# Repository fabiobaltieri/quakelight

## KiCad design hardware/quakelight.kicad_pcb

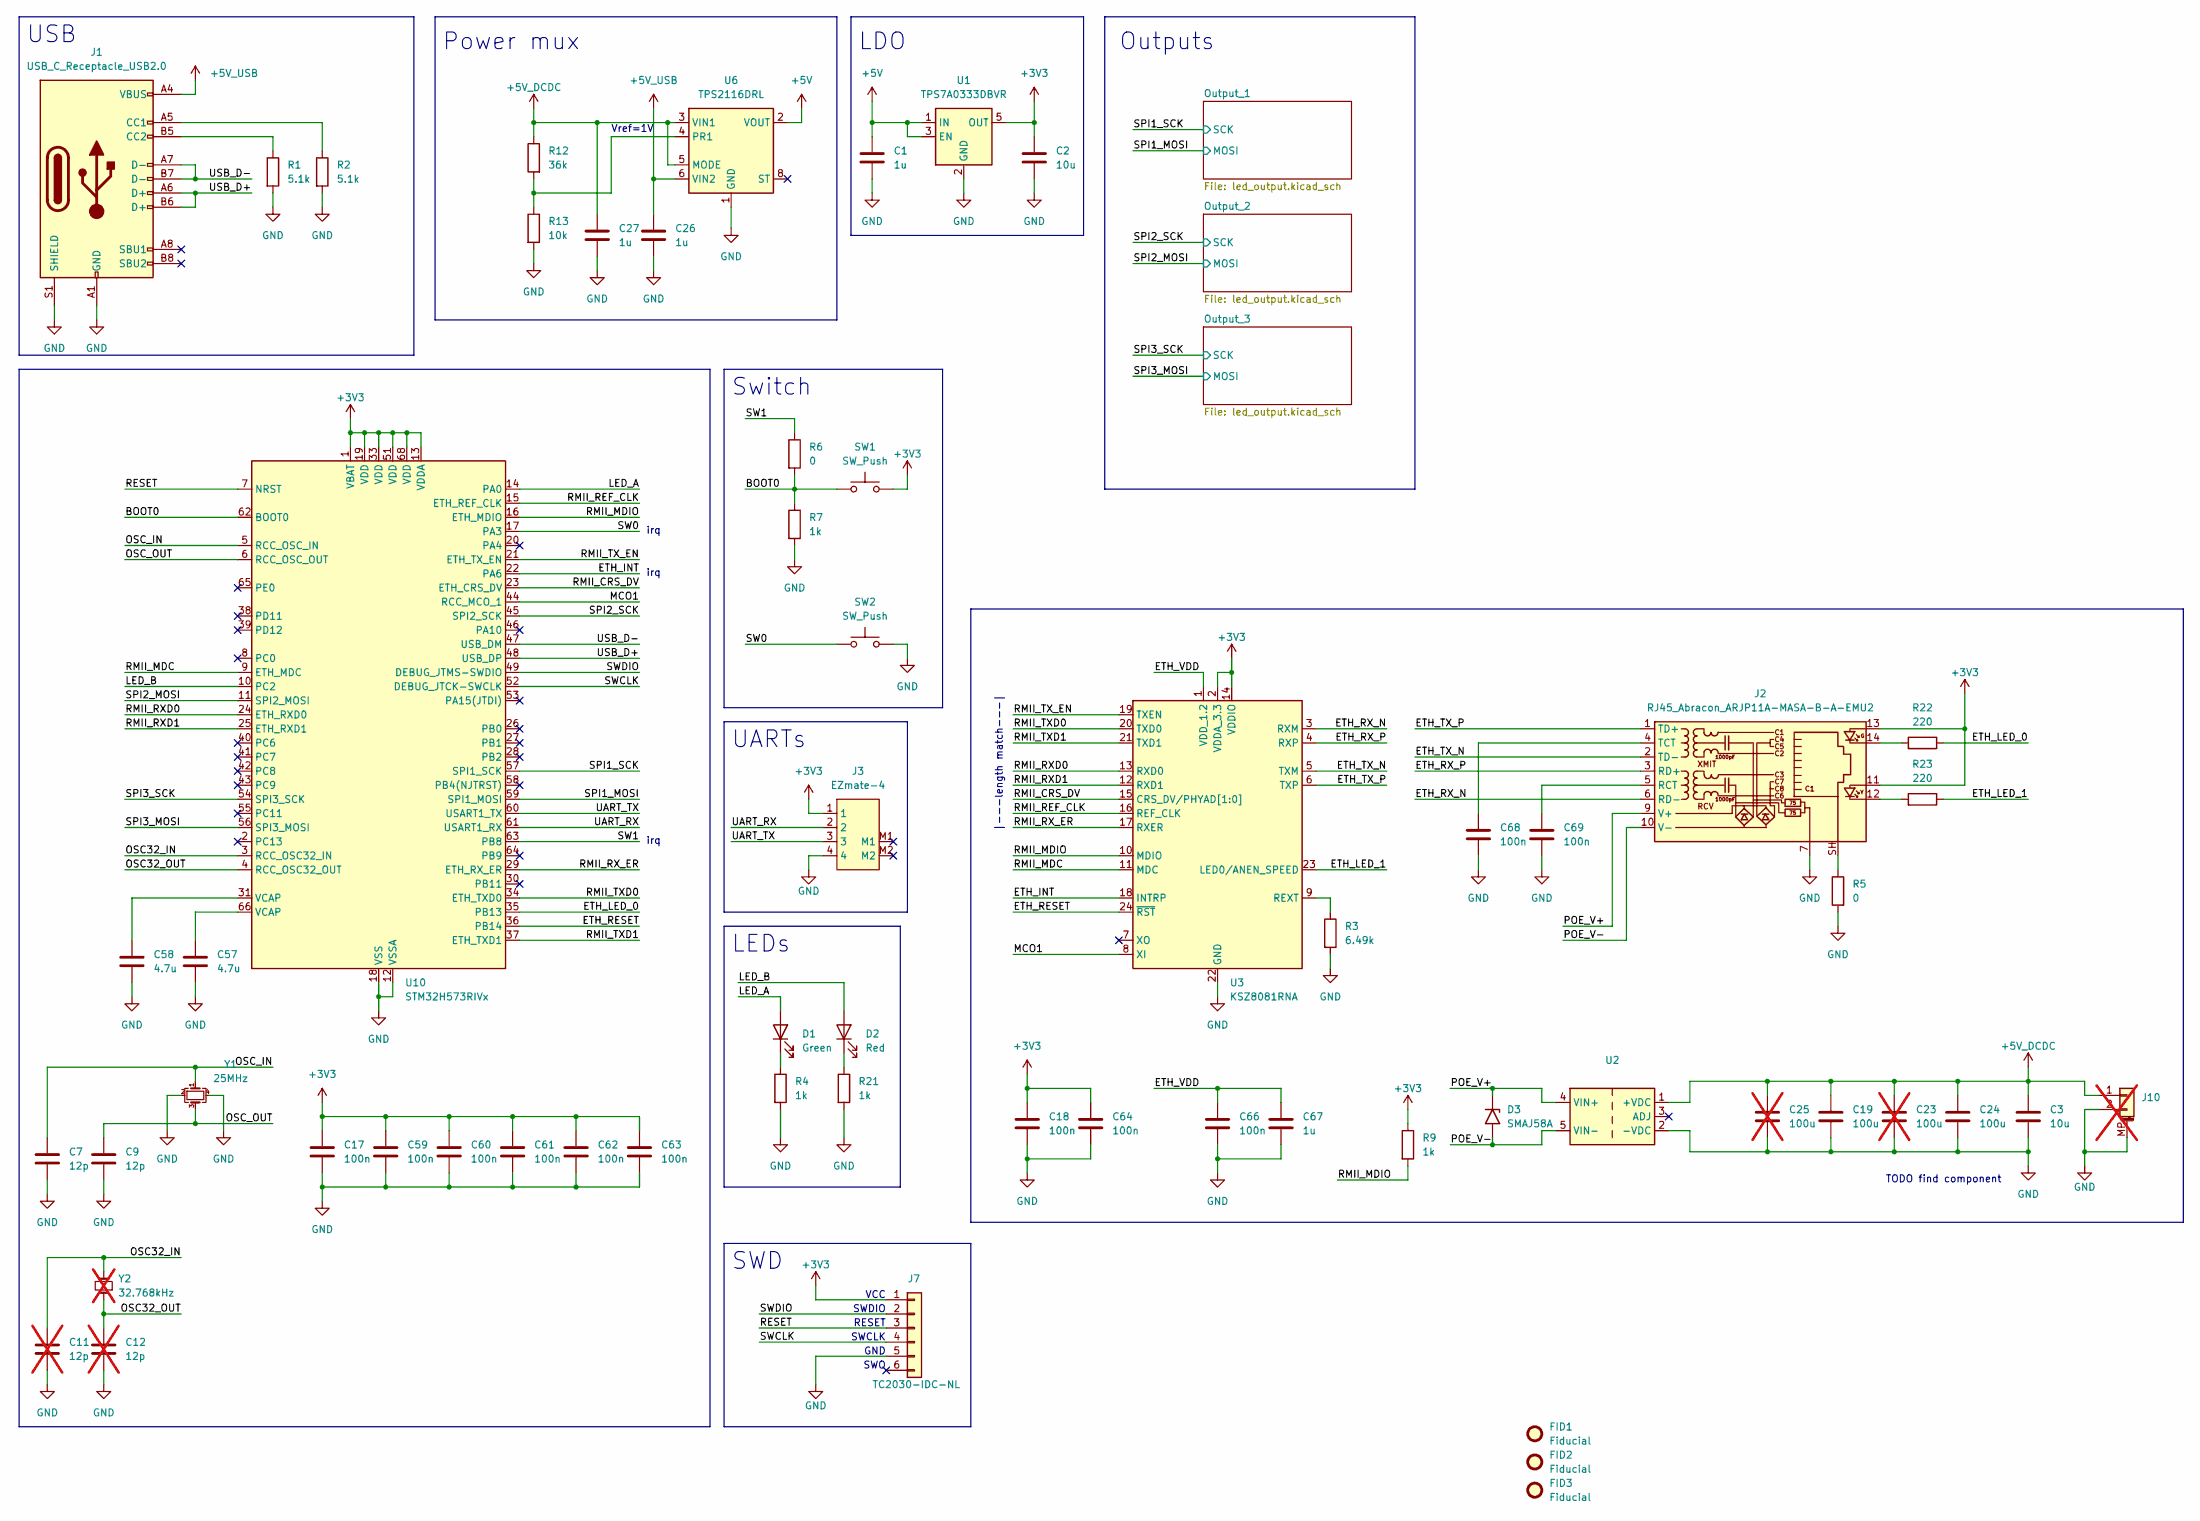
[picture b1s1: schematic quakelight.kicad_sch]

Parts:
C1, C26, C27, C67: 1u; C_0402_Worthington
C2, C3: 10u; C_0402_Worthington
C7, C9: 12p; C_0402_Worthington
C11, C12: 12p; C_0402_Worthington; not fitted
C17, C18, C59, C60, C61, C62, C63, C64, C66, C68, C69: 100n; C_0402_Worthington
C19, C24: 100u; C_1206_3216Metric
C23, C25: 100u; C_1206_3216Metric; not fitted
C57, C58: 4.7u; C_0402_Worthington
D1: Green; LED_0402_Worthington
D2: Red; LED_0402_Worthington
D3: SMAJ58A; D_SMA
FID1, FID2, FID3: Fiducial; Fiducial_0.75mm_Mask1.5mm
J1: USB_C_Receptacle_USB2.0; USB_C_Receptacle_JAE_DX07S016JA1R1500
J2: RJ45_Abracon_ARJP11A-MASA-B-A-EMU2; RJ45_Abracon_ARJP11A-MA_Horizontal
J3: EZmate-4
J7: TC2030-IDC-NL; Tag-Connect_TC2030-IDC-NL_2x03_P1.27mm_Vertical
J10: Conn_01x02_MountingPin; JST_PH_S2B-PH-SM4-TB_1x02-1MP_P2.00mm_Horizontal; not fitted
R1, R2: 5.1k; R_0402_Worthington
R3: 6.49k; R_0402_Worthington
R4, R7, R9, R21: 1k; R_0402_Worthington
R5: 0; R_0805_2012Metric
R6: 0; R_0402_Worthington
R12: 36k; R_0402_Worthington
R13: 10k; R_0402_Worthington
R22, R23: 220; R_0402_Worthington
SW1, SW2: SW_Push; SW_Push_1P1T_NO_Vertical_Wuerth_434133025816
U1: TPS7A0333DBVR; SOT-23-5
U2: AG9900-MTB
U3: KSZ8081RNA; QFN-24-1EP_4x4mm_P0.5mm_EP2.6x2.6mm
U6: TPS2116DRL; SOT-583-8
U10: STM32H573RIVx; QFN-68-1EP_8x8mm_P0.4mm_EP6.4x6.4mm
Y1: 25MHz; Crystal_SMD_2016-4Pin_2.0x1.6mm
Y2: 32.768kHz; Crystal_SMD_2012-2Pin_2.0x1.2mm; not fitted

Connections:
+3V3: C2.1, C17.1, C18.1, C59.1, C60.1, C61.1, C62.1, C63.1, C64.1, J2.11, J2.13, J3.1, J7.1, R9.1, SW1.2, U1.5 (OUT), U3.2 (VDDA_3.3), U3.14 (VDDIO), U10.1 (VBAT), U10.13 (VDDA), U10.19 (VDD), U10.33 (VDD), U10.51 (VDD), U10.68 (VDD); also elsewhere on the board
+5V: C1.1, U1.1 (IN), U1.3 (EN), U6.2 (VOUT), U6.7 (VOUT); also elsewhere on the board
+5V_DCDC: C3.1, C19.1, C23.1, C24.1, C25.1, C27.1, J10.1, R12.1, U2.1 (+VDC), U6.3 (VIN1), U6.5 (MODE)
+5V_USB: C26.1, J1.A4 (VBUS), J1.A9 (VBUS), J1.B4 (VBUS), J1.B9 (VBUS), U6.6 (VIN2)
/BOOT0: R6.2, R7.1, SW1.1, U10.62 (BOOT0)
/ETH_INT: U3.18 (INTRP), U10.22 (PA6)
/ETH_LED_0: R22.1, U10.35 (PB13)
/ETH_LED_1: R23.1, U3.23 (LED0/ANEN_SPEED)
/ETH_RESET: U3.24 (~RST), U10.36 (PB14)
/ETH_RX_N: J2.6 (RD-), U3.3 (RXM)
/ETH_RX_P: J2.3 (RD+), U3.4 (RXP)
/ETH_TX_N: J2.2 (TD-), U3.5 (TXM)
/ETH_TX_P: J2.1 (TD+), U3.6 (TXP)
/ETH_VDD: C66.1, C67.1, U3.1 (VDD_1.2)
/LED_A: D1.2 (A), U10.14 (PA0)
/LED_B: D2.2 (A), U10.10 (PC2)
/MCO1: U3.8 (XI), U10.44 (RCC_MCO_1)
/OSC32_IN: C11.1, U10.3 (RCC_OSC32_IN), Y2.2
/OSC32_OUT: C12.1, U10.4 (RCC_OSC32_OUT), Y2.1
/OSC_IN: C7.1, U10.5 (RCC_OSC_IN), Y1.1
/OSC_OUT: C9.1, U10.6 (RCC_OSC_OUT), Y1.3
/POE_V+: D3.1 (A1), J2.9 (V+), U2.4 (VIN+)
/POE_V-: D3.2 (A2), J2.10 (V-), U2.5 (VIN-)
/RESET: J7.3, U10.7 (NRST)
/RMII_CRS_DV: U3.15 (CRS_DV/PHYAD[1:0]), U10.23 (ETH_CRS_DV)
/RMII_MDC: U3.11 (MDC), U10.9 (ETH_MDC)
/RMII_MDIO: R9.2, U3.10 (MDIO), U10.16 (ETH_MDIO)
/RMII_REF_CLK: U3.16 (REF_CLK), U10.15 (ETH_REF_CLK)
/RMII_RXD0: U3.13 (RXD0), U10.24 (ETH_RXD0)
/RMII_RXD1: U3.12 (RXD1), U10.25 (ETH_RXD1)
/RMII_RX_ER: U3.17 (RXER), U10.29 (ETH_RX_ER)
/RMII_TXD0: U3.20 (TXD0), U10.34 (ETH_TXD0)
/RMII_TXD1: U3.21 (TXD1), U10.37 (ETH_TXD1)
/RMII_TX_EN: U3.19 (TXEN), U10.21 (ETH_TX_EN)
/SPI1_MOSI: U10.59 (SPI1_MOSI); also elsewhere on the board
/SPI1_SCK: U10.57 (SPI1_SCK); also elsewhere on the board
/SPI2_MOSI: U10.11 (SPI2_MOSI); also elsewhere on the board
/SPI2_SCK: U10.45 (SPI2_SCK); also elsewhere on the board
/SPI3_MOSI: U10.56 (SPI3_MOSI); also elsewhere on the board
/SPI3_SCK: U10.54 (SPI3_SCK); also elsewhere on the board
/SW0: SW2.1, U10.17 (PA3)
/SW1: R6.1, U10.63 (PB8)
/SWCLK: J7.4, U10.52 (DEBUG_JTCK-SWCLK)
/SWDIO: J7.2, U10.49 (DEBUG_JTMS-SWDIO)
/UART_RX: J3.2, U10.61 (USART1_RX)
/UART_TX: J3.3, U10.60 (USART1_TX)
/USB_D+: J1.A6 (D+), J1.B6 (D+), U10.48 (USB_DP)
/USB_D-: J1.A7 (D-), J1.B7 (D-), U10.47 (USB_DM)
GND: C1.2, C2.2, C3.2, C7.2, C9.2, C11.2, C12.2, C17.2, C18.2, C19.2, C23.2, C24.2, C25.2, C26.2, C27.2, C57.2, C58.2, C59.2, C60.2, C61.2, C62.2, C63.2, C64.2, C66.2, C67.2, C68.2, C69.2, J1.A1 (GND), J1.A12 (GND), J1.B1 (GND), J1.B12 (GND), J1.S1 (SHIELD), J2.7, J3.4, J7.5, J10.2, J10.MP (MountPin), R1.2, R2.2, R3.2, R4.2, R5.2, R7.2, R13.2, R21.2, SW2.2, U1.2 (GND), U2.2 (-VDC), U3.22 (GND), U3.25 (GND), U6.1 (GND), U10.12 (VSSA), U10.18 (VSS), U10.32 (VSS), U10.50 (VSS), U10.67 (VSS), U10.69 (VSS), Y1.2, Y1.4; also elsewhere on the board
unnamed: C57.1, U10.66 (VCAP)
unnamed: C58.1, U10.31 (VCAP)
unnamed: D1.1 (K), R4.1
unnamed: D2.1 (K), R21.1
unnamed: J1.A5 (CC1), R2.1
unnamed: J1.B5 (CC2), R1.1
unnamed: J2.12, R23.2
unnamed: J2.14, R22.2
unnamed: J2.SH, R5.1
unnamed: C69.1, J2.5 (RCT)
unnamed: C68.1, J2.4 (TCT)
unnamed: R3.1, U3.9 (REXT)
unnamed: R12.2, R13.1, U6.4 (PR1)

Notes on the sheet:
RESET
Outputs
irq
USB
SWD
|---length match---|
LEDs
SWDIO
TODO find component
GND
SWO
Switch
Vref=1V
SWCLK
Power mux
LDO
UARTs
VCC

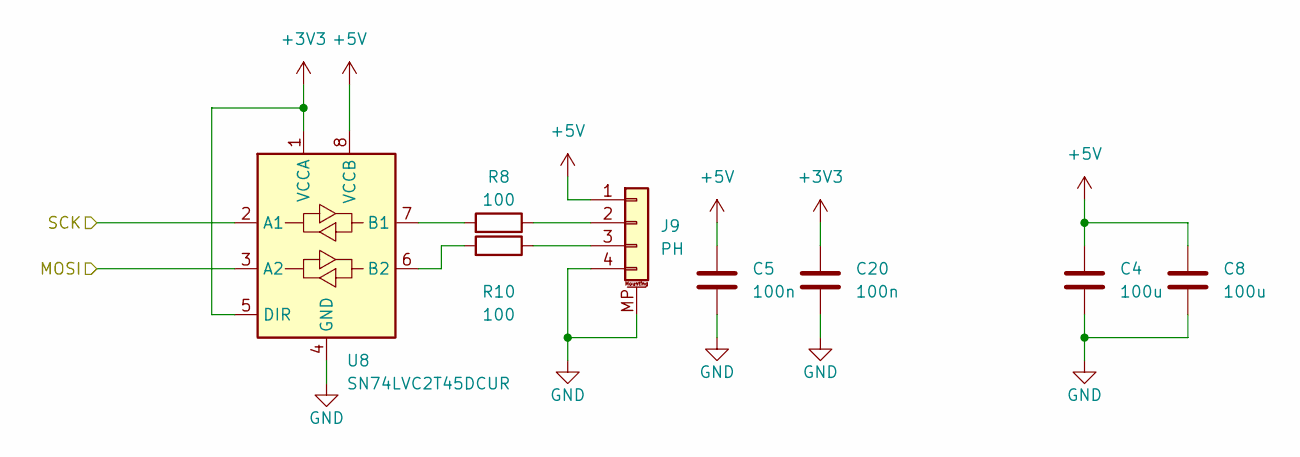
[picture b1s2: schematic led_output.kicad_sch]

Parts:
C4, C8: 100u; C_1206_3216Metric
C5, C20: 100n; C_0402_Worthington
J9: PH; JST_PH_S4B-PH-SM4-TB_1x04-1MP_P2.00mm_Horizontal
R8, R10: 100; R_0402_Worthington
U8: SN74LVC2T45DCUR; VSSOP-8_2.3x2mm_P0.5mm

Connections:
+3V3: C20.1, U8.1 (VCCA), U8.5 (DIR); also elsewhere on the board
+5V: C4.1, C5.1, C8.1, J9.1, U8.8 (VCCB); also elsewhere on the board
/SPI1_MOSI: U8.3 (A2); also elsewhere on the board
/SPI1_SCK: U8.2 (A1); also elsewhere on the board
GND: C4.2, C5.2, C8.2, C20.2, J9.4, J9.MP (MountPin), U8.4 (GND); also elsewhere on the board
unnamed: J9.2, R8.1
unnamed: J9.3, R10.1
unnamed: R8.2, U8.7 (B1)
unnamed: R10.2, U8.6 (B2)

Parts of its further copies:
C6, C10, C21, C22: 100n; C_0402_Worthington
C13, C14, C15, C16: 100u; C_1206_3216Metric
J4, J5: PH; JST_PH_S4B-PH-SM4-TB_1x04-1MP_P2.00mm_Horizontal
R11, R14, R15, R16: 100; R_0402_Worthington
U4, U5: SN74LVC2T45DCUR; VSSOP-8_2.3x2mm_P0.5mm

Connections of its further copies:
+3V3: C21.1, C22.1, U4.1 (VCCA), U4.5 (DIR), U5.1 (VCCA), U5.5 (DIR); also elsewhere on the board
+5V: C6.1, C10.1, C13.1, C14.1, C15.1, C16.1, J4.1, J5.1, U4.8 (VCCB), U5.8 (VCCB); also elsewhere on the board
/SPI2_MOSI: U4.3 (A2); also elsewhere on the board
/SPI2_SCK: U4.2 (A1); also elsewhere on the board
/SPI3_MOSI: U5.3 (A2); also elsewhere on the board
/SPI3_SCK: U5.2 (A1); also elsewhere on the board
GND: C6.2, C10.2, C13.2, C14.2, C15.2, C16.2, C21.2, C22.2, J4.4, J4.MP (MountPin), J5.4, J5.MP (MountPin), U4.4 (GND), U5.4 (GND); also elsewhere on the board
unnamed: J4.2, R11.1
unnamed: J4.3, R14.1
unnamed: J5.2, R15.1
unnamed: J5.3, R16.1
unnamed: R11.2, U4.7 (B1)
unnamed: R14.2, U4.6 (B2)
unnamed: R15.2, U5.7 (B1)
unnamed: R16.2, U5.6 (B2)

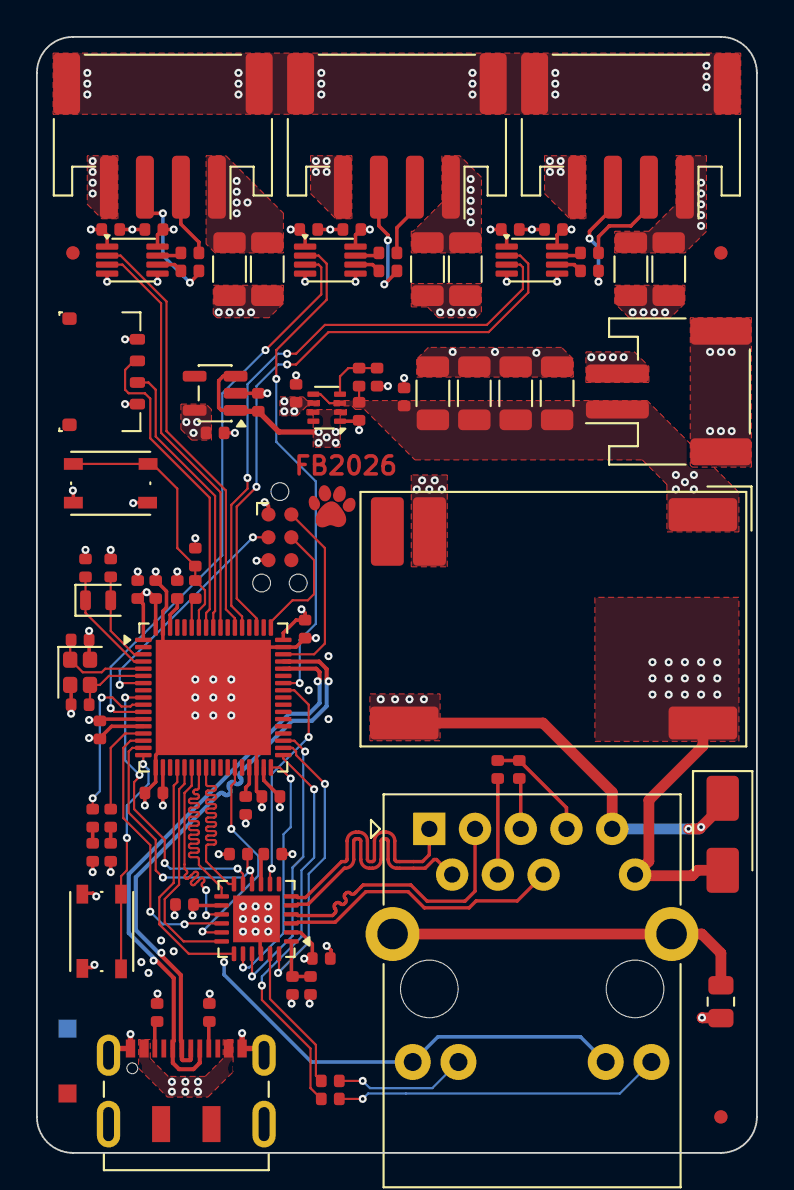
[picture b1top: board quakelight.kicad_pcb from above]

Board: 4 copper layers, 40.0 x 62.0 mm, 84 parts (0 on the bottom side), 74 nets.

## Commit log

2025-12-21 hw: move output on separate sheet
2025-12-22 fw: initial import
2025-12-22 fw: wait for if up rather than address
2025-12-25 fw: add quakelight board
2025-12-25 hw: 3d model update
2025-12-25 fw: add net_led
2025-12-25 fw: add led dev check
2025-12-25 fw: add wifi_creds
2025-12-25 fw: use full ram
2025-12-25 fw: enable sensors
2025-12-25 fw: add xiao config, use wifi creds
2025-12-25 fw: drop stale include
2025-12-25 fw: add i2s channel to esp32c3
2025-12-25 fw: add rpi pico config
2025-12-25 fw: add temp logger
2025-12-25 fw: use real spi and dma for rp2040
2025-12-27 fw: use LOG for temp logging
2025-12-27 add a .gitignore file
2025-12-29 fw: listener cleanup
2025-12-30 fw: add keepalive
2026-01-01 hw: add few notes
2026-01-08 fw: tweaks few net configs
2026-01-08 fw: add frdm_mcxn947_mcxn947_cpu0.overlay
2026-01-17 hw: dnp update
2026-02-11 add flood.py heartbeat_listen.py
2026-02-12 fw: add leds.c
2026-02-12 fw: add sequence check code
2026-02-12 add workflow and west.yml
2026-02-12 fw: add few num_pixel check, fix compiler warning
2026-02-12 fw: set wifi data for rp2040w
2026-02-12 build: add few more boards
2026-02-14 build: fetch retry
2026-02-18 fw: default to dfu-util
